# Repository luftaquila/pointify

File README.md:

# Pointify

DIY retro analog gauge meters that display system metrics in real time, including Claude usage stats!

<table>
  <tr>
    <td>
      
    </td>
    <td>
      <video src="https://github.com/user-attachments/assets/7dd133b8-86af-4e1a-b1fe-1c4ecdfecce1" controls></video>
    </td>
  </tr>
</table>

## Usage

Pointify Desktop runs on macOS, Windows, and Linux, driving up to 8 gauges with customizable metrics.

Its software gauges work without the device, but watching real needles twitch is way better. So go build one!

1. Install Pointify Desktop and open it.
    * **macOS / Linux (Homebrew)**
      ```bash
      brew tap luftaquila/pointify https://github.com/luftaquila/pointify
      brew install --cask pointify # macOS
      brew install pointify        # Linux
      ```
    * **Windows (Manual)**: Download from the [latest release](https://github.com/luftaquila/pointify/releases/latest).
1. Connect your Pointify to the computer and set up gauges to your preference.

<details>

<summary>Full list of supported metrics</summary>

- 🕹️ Hardware
  - CPU
    - Utilization
    - Temperature
    - Clock Frequency
    - Power Consumption
  - GPU
    - Utilization
    - Temperature
    - Clock Frequency
    - Power Consumption
    - VRAM Usage
  - Memory
    - RAM and Swap Usage
  - Network
    - RX, TX and RX/TX Speed
  - Disk
    - Usage
    - Read, Write and R/W Speed
- **🤖 Claude Usage Stats**
  - Usage Limits
    - 5h session limit and reset time
    - Weekly limit and reset time
  - Claude Code stats
    - Today's total tokens
    - Today's input, output and I/O tokens
    - Today's cache read and write tokens
    - Today's cost ($)

</details>

> [!NOTE]
> Some metrics have platform/hardware limitations.
> * **CPU Temperature and Power**: Not available on Windows.
> * **GPU metrics**: Not supported on AMD graphics cards.
> * **GPU VRAM Usage**: Not available on Apple Silicon.

### Optional setup

To fetch Claude usage limits (5h session and weekly), Pointify needs your browser credentials.

Claude Code stats are collected from local logs and do not require credentials.

> [!NOTE]
> Credentials are stored locally and only used to fetch usage data directly from Claude. No information is sent to any third-party server.
> See the `get_claude_usage` function in [lib.rs](https://github.com/luftaquila/pointify/blob/v2/gui/src-tauri/src/lib.rs) for details.

<details>

<summary>Firefox</summary>

1. Open Firefox and visit `https://claude.ai`. Log in if you haven't already.
1. Open Developer Tools (F12).
1. Go to the `Storage` tab.
1. On the left sidebar, click `Cookies` - `https://claude.ai`.
1. Locate the `cf_clearance`, `lastActiveOrg`, and `sessionKey` values.
1. Click the `Open .claude.env` button on the desktop app and paste the corresponding values.

</details>

<details>

<summary>Chrome</summary>

1. Open Chrome and visit `https://claude.ai`. Log in if you haven't already.
1. Open Developer Tools (F12).
1. Go to the `Application` tab.
1. On the left sidebar, click `Storage` - `Cookies` - `https://claude.ai`.
1. Locate the `cf_clearance`, `lastActiveOrg`, and `sessionKey` values.
1. Click the `Open .claude.env` button on the desktop app and paste the corresponding values.

</details>

## Do It Yourself!

Pointify is fully open-source and open-hardware. Build your own device at home!

### 1. Build PCB

1. Download `pointify-hardware.zip` from the [latest release](https://github.com/luftaquila/pointify/releases/latest) and unzip.
1. Gerber, BOM, and CPL files are in the `pcb/` directory. Use them to place a PCB assembly order from manufacturers such as JLCPCB.

### 2. Upload Firmware

If your board is fresh and the MCU has never been flashed, it will always boot into USB bootloader mode.

1. Connect your board to the computer.
1. Open Pointify Desktop and click the chip icon at the bottom of the sidebar.

`CURRENT` version will show as `Bootloader`. Click the `Update Firmware` button to flash it.

> [!NOTE]
> If your computer is running Windows and `CURRENT` shows as `N/A`, it means the CH372 driver is missing.
> Press the `Shift` key and the button will change to `Update Firmware (force)`.
> The force install process will automatically detect and install the missing driver.
> Alternatively, you can install the driver manually from [here](https://www.wch-ic.com/downloads/CH372DRV_EXE.html).

### 3. 3D-Print Housing and Assembly

#### Prerequisites

* 6x M2*8mm bolts
* 91C4 3V DC analog voltmeters, as many as you need
* Some wires and soldering skills
* 4x anti-slip pads with radius < 10mm

1. Download `pointify-hardware.zip` from the [latest release](https://github.com/luftaquila/pointify/releases/latest) and unzip.
1. 3D-print the STL files you need from the `3d/` directory.
1. Install the gauges into the housing.
1. Connect all negative terminals (near the 0V scale) of the gauge to the GND header on the PCB.
    * Daisy-chain them, since there's only one GND pad (marked ⏚).
1. Connect each positive terminal (near the 3V scale) to PWM port #1~8 on the PCB.
    * The pad right next to the GND is PWM1.
    * Solder directly to the washer that comes with the gauge, or crimp a ring terminal onto the wire. Crimping is easier to work with but you'll need a crimp tool and ring terminals.
1. Mount the PCB upside down onto the housing. The USB port faces downward.
1. Attach the back cover.

### 4. Customize Gauge Panel

Use the [Gauge Panel Generator](https://luftaquila.github.io/pointify/generator.html) to design and print your own gauge panel graphics.

Examples from the [device/gauge/example/](device/gauge/example) directory:

## Development

<details>

<summary>Open</summary>

### Desktop App

Requires [Node.js](https://nodejs.org/en/download) and [Rust](https://rust-lang.org/tools/install/).

```bash
cd gui
npm install
npm run tauri dev       # development
npm run tauri build     # production
```

### Firmware

Requires [nightly Rust](https://rust-lang.github.io/rustup/concepts/channels.html#working-with-nightly-rust).

```bash
cargo install wchisp --git https://github.com/ch32-rs/wchisp

cd device/firmware
cargo build --release   # build only
cargo run --release     # build + flash
```

</details>

<hr>
<br>

<picture>
  <source media="(prefers-color-scheme: dark)" srcset="https://api.star-history.com/svg?repos=luftaquila/pointify&type=Date&theme=dark" />
  <source media="(prefers-color-scheme: light)" srcset="https://api.star-history.com/svg?repos=luftaquila/pointify&type=Date" />
  
</picture>

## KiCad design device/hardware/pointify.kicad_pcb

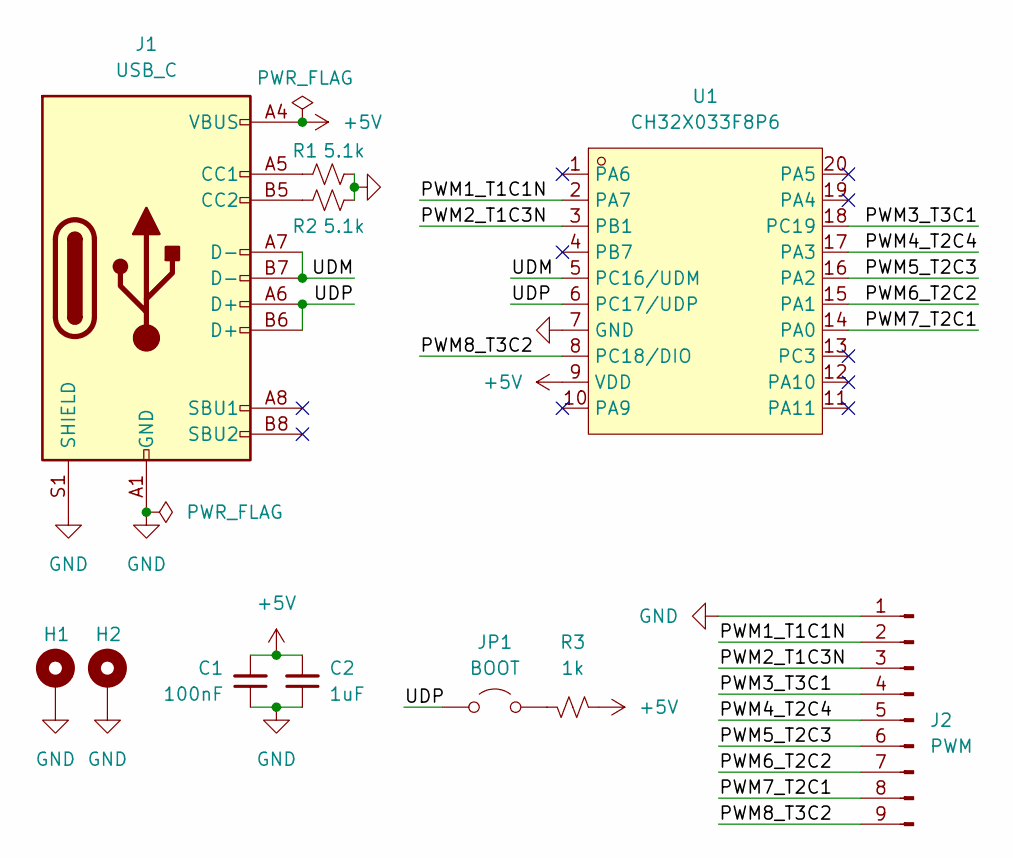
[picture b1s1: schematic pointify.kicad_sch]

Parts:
C1: 100nF; C_0402_1005Metric; LCSC C1525
C2: 1uF; C_0402_1005Metric; LCSC C52923
H1, H2: MountingHole_Pad; MountingHole_3.7mm_Pad_TopBottom; LCSC C2916384
J1: USB_C; USB_C_Receptacle_GCT_USB4105-xx-A_16P_TopMnt_Horizontal; LCSC C2927038
J2: PWM; PinHeader_1x09_P2.54mm_Vertical
JP1: BOOT; PinHeader_1x02_P2.00mm_Vertical
R1, R2: 5.1k; R_0402_1005Metric; LCSC C25905
R3: 1k; R_0402_1005Metric; LCSC C11702
U1: CH32X033F8P6; TSSOP-20_4.4x6.5mm_P0.65mm; LCSC Part C19268290

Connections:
+5V: C1.2, C2.2, J1.A4 (VBUS), J1.A9 (VBUS), J1.B4 (VBUS), J1.B9 (VBUS), R3.1, U1.9 (VDD)
/PWM1_T1C1N: J2.2, U1.2 (PA7)
/PWM2_T1C3N: J2.3, U1.3 (PB1)
/PWM3_T3C1: J2.4, U1.18 (PC19)
/PWM4_T2C4: J2.5, U1.17 (PA3)
/PWM5_T2C3: J2.6, U1.16 (PA2)
/PWM6_T2C2: J2.7, U1.15 (PA1)
/PWM7_T2C1: J2.8, U1.14 (PA0)
/PWM8_T3C2: J2.9, U1.8 (PC18/DIO)
/UDM: J1.A7 (D-), J1.B7 (D-), U1.5 (PC16/UDM)
/UDP: J1.A6 (D+), J1.B6 (D+), JP1.2 (B), U1.6 (PC17/UDP)
GND: C1.1, C2.1, H1.1, H2.1, J1.A1 (GND), J1.A12 (GND), J1.B1 (GND), J1.B12 (GND), J1.S1 (SHIELD), J2.1, R1.2, R2.2, U1.7 (GND)
unnamed: J1.A5 (CC1), R1.1
unnamed: J1.B5 (CC2), R2.1
unnamed: JP1.1 (A), R3.2

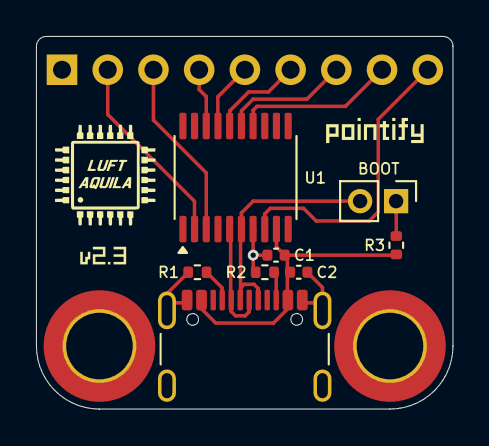
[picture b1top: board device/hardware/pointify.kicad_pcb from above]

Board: 2 copper layers, 23.1 x 20.7 mm, 11 parts (0 on the bottom side), 15 nets.

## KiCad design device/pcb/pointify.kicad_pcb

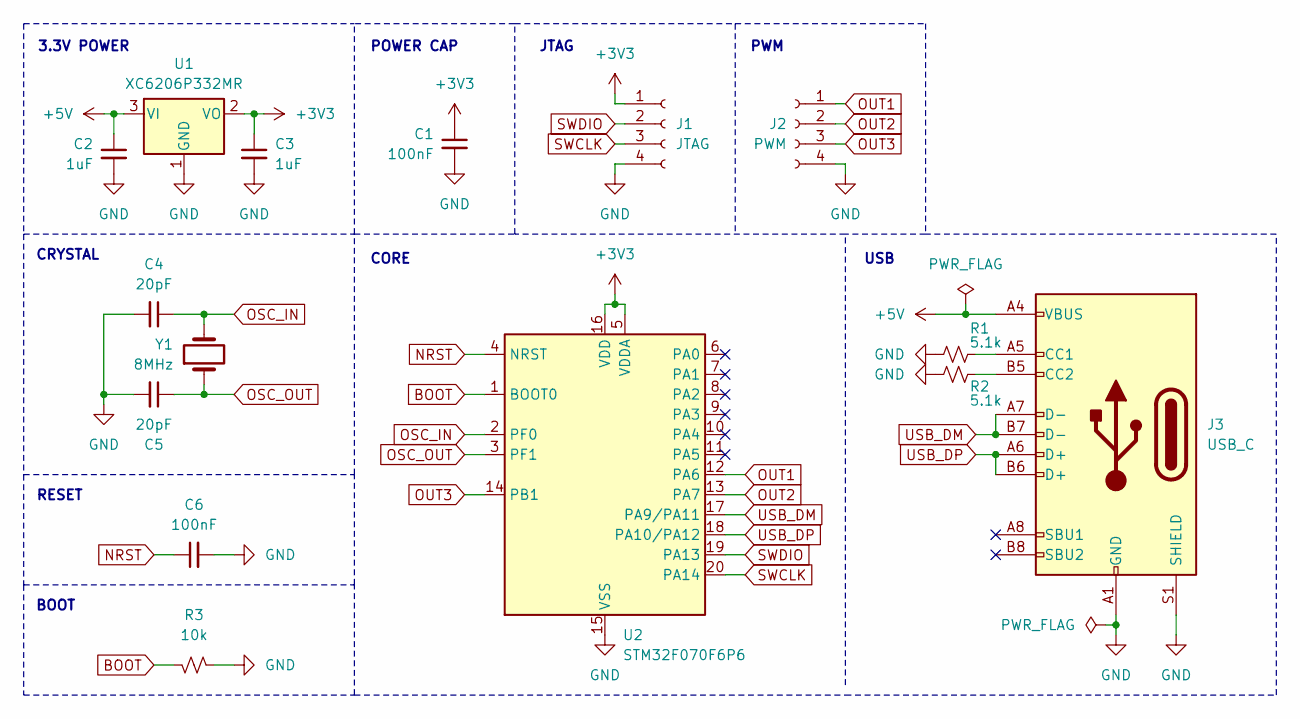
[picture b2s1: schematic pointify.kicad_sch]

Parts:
C1, C6: 100nF; C_0603_1608Metric; LCSC C14663
C2, C3: 1uF; C_0603_1608Metric; LCSC C15849
C4, C5: 20pF; C_0603_1608Metric; LCSC C1648
J1: JTAG; PinHeader_1x04_P1.27mm_Vertical
J2: PWM; PinHeader_1x04_P2.54mm_Vertical
J3: USB_C; USB_C_Receptacle_GCT_USB4105-xx-A_16P_TopMnt_Horizontal; LCSC C165948
R1, R2: 5.1k; R_0603_1608Metric; LCSC C23186
R3: 10k; R_0603_1608Metric; LCSC C25804
U1: XC6206P332MR; SOT-23-3; LCSC C5446
U2: STM32F070F6P6; TSSOP-20_4.4x6.5mm_P0.65mm; LCSC C86951
Y1: 8MHz; Crystal_SMD_5032-2Pin_5.0x3.2mm; LCSC C115962

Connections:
+3V3: C1.1, C3.1, J1.1, U1.2 (VO), U2.5 (VDDA), U2.16 (VDD)
+5V: C2.1, J3.A4 (VBUS), J3.A9 (VBUS), J3.B4 (VBUS), J3.B9 (VBUS), U1.3 (VI)
BOOT: R3.2, U2.1 (BOOT0)
GND: C1.2, C2.2, C3.2, C4.2, C5.2, C6.2, J1.4, J2.4, J3.A1 (GND), J3.A12 (GND), J3.B1 (GND), J3.B12 (GND), J3.S1 (SHIELD), R1.1, R2.1, R3.1, U1.1 (GND), U2.15 (VSS)
NRST: C6.1, U2.4 (NRST)
unnamed: J3.A5 (CC1), R1.2
unnamed: J3.B5 (CC2), R2.2
OSC_IN: C4.1, U2.2 (PF0), Y1.2
OSC_OUT: C5.1, U2.3 (PF1), Y1.1
OUT1: J2.1, U2.12 (PA6)
OUT2: J2.2, U2.13 (PA7)
OUT3: J2.3, U2.14 (PB1)
SWCLK: J1.3, U2.20 (PA14)
SWDIO: J1.2, U2.19 (PA13)
USB_DM: J3.A7 (D-), J3.B7 (D-), U2.17 (PA9/PA11)
USB_DP: J3.A6 (D+), J3.B6 (D+), U2.18 (PA10/PA12)

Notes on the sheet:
CRYSTAL
USB
POWER CAP
PWM
JTAG
3.3V POWER
CORE
BOOT
RESET

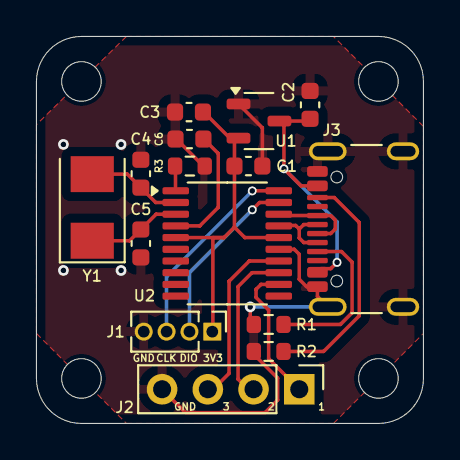
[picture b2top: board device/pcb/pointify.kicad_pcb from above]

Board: 2 copper layers, 21.5 x 21.5 mm, 15 parts (0 on the bottom side), 16 nets.

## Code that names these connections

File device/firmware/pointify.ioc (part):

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Mcu.Name=STM32F070F6Px
Mcu.Package=TSSOP20
Mcu.UserName=STM32F070F6Px
PA11.Mode=Device
PA11.Signal=USB_DM
PA12.Mode=Device
PA12.Signal=USB_DP
PA13.Mode=Serial_Wire
PA13.Signal=SYS_SWDIO
PA14.Mode=Serial_Wire
PA14.Signal=SYS_SWCLK
PA6.Signal=S_TIM3_CH1
PA7.Signal=S_TIM3_CH2
PB1.Signal=S_TIM3_CH4
PF0-OSC_IN.Mode=HSE-External-Oscillator
PF0-OSC_IN.Signal=RCC_OSC_IN
PF1-OSC_OUT.Mode=HSE-External-Oscillator
PF1-OSC_OUT.Signal=RCC_OSC_OUT
RCC.SYSCLKFreq_VALUE=48000000
RCC.SYSCLKSource=RCC_SYSCLKSOURCE_PLLCLK
board=custom

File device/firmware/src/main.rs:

#![no_std]
#![no_main]
#![feature(type_alias_impl_trait)]
#![feature(impl_trait_in_assoc_type)]

mod usb_cdc;

use ch32_hal as hal;
use embassy_executor::Spawner;
use hal::adc::{Adc, SampleTime, VrefInt};
use hal::time::Hertz;
use hal::timer::complementary_pwm::{ComplementaryPwm, ComplementaryPwmPin};
use hal::timer::low_level::CountingMode;
use hal::timer::simple_pwm::{PwmPin, SimplePwm};
use hal::timer::Channel;

#[embassy_executor::main(entry = "qingke_rt::entry")]
async fn main(_spawner: Spawner) -> ! {
    let mut config = hal::Config::default();
    config.rcc = hal::rcc::Config::SYSCLK_FREQ_48MHZ_HSI;
    let p = hal::init(config);

    // ADC
    let mut adc = Adc::new(p.ADC1, Default::default());
    let mut vrefint = VrefInt;
    let vref_raw = adc.convert(&mut vrefint, SampleTime::CYCLES11) as u32;
    let is_5v_supply = vref_raw < 1200;

    // TIM2 remap=0: PA0, PA1, PA2, PA3
    let ch1 = PwmPin::new_ch1::<0>(p.PA0);
    let ch2 = PwmPin::new_ch2::<0>(p.PA1);
    let ch3 = PwmPin::new_ch3::<0>(p.PA2);
    let ch4 = PwmPin::new_ch4::<0>(p.PA3);
    let mut pwm_tim2 = SimplePwm::new(
        p.TIM2, Some(ch1), Some(ch2), Some(ch3), Some(ch4),
        Hertz::khz(1), CountingMode::default(),
    );
    pwm_tim2.enable(Channel::Ch1);
    pwm_tim2.enable(Channel::Ch2);
    pwm_tim2.enable(Channel::Ch3);
    pwm_tim2.enable(Channel::Ch4);

    // Release PC18/DIO and PC19/DCK debug pins for GPIO/timer use
    // AFIO_PCFR1 bits[26:24] = sw_cfg = 0b100 (disable debug, release both pins)
    unsafe {
        let afio_pcfr1 = 0x4001_0004 as *mut u32;
        let val = afio_pcfr1.read_volatile();
        afio_pcfr1.write_volatile((val & !(0x07 << 24)) | (0x04 << 24));
    }

    // TIM3 remap=2: PC19(CH1), PC18(CH2)
    let ch1_t3 = PwmPin::new_ch1::<2>(p.PC19);
    let ch2_t3 = PwmPin::new_ch2::<2>(p.PC18);
    let mut pwm_tim3 = SimplePwm::new(
        p.TIM3, Some(ch1_t3), Some(ch2_t3), None, None,
        Hertz::khz(1), CountingMode::default(),
    );
    pwm_tim3.enable(Channel::Ch1);
    pwm_tim3.enable(Channel::Ch2);

    // TIM1 remap=1: PA7(CH1N), PB1(CH3N)
    let ch1n = ComplementaryPwmPin::new_ch1::<1>(p.PA7);
    let ch3n = ComplementaryPwmPin::new_ch3::<1>(p.PB1);
    let mut pwm_tim1 = ComplementaryPwm::new(
        p.TIM1, None, Some(ch1n), None, None, None, Some(ch3n), None,
        Hertz::khz(1), CountingMode::default(),
    );
    pwm_tim1.set_dead_time(0);
    pwm_tim1.enable(Channel::Ch1);
    pwm_tim1.enable(Channel::Ch3);

    // HAL ComplementaryPwm doesn't work properly with N-only channels.
    // Configure TIM1 entirely via raw registers.
    const TIM1: usize = 0x4001_2C00;
    unsafe {
        // CR1: CEN (bit 0) = 1 — start counter
        let cr1 = (TIM1 + 0x00) as *mut u32;
        let v = cr1.read_volatile();
        cr1.write_volatile(v | 1);
        // CCMR1: OC1M = PWM mode 2 (0b111), OC1PE = 1
        let ccmr1 = (TIM1 + 0x18) as *mut u32;
        let v = ccmr1.read_volatile();
        ccmr1.write_volatile((v & !(0x7 << 4)) | (0x7 << 4) | (1 << 3));
        // CCMR2: OC3M = PWM mode 2 (0b111), OC3PE = 1
        let ccmr2 = (TIM1 + 0x1C) as *mut u32;
        let v = ccmr2.read_volatile();
        ccmr2.write_volatile((v & !(0x7 << 4)) | (0x7 << 4) | (1 << 3));
        // CCER: CC1NE (bit 2) = 1, CC3NE (bit 10) = 1
        let ccer = (TIM1 + 0x20) as *mut u32;
        let v = ccer.read_volatile();
        ccer.write_volatile(v | (1 << 2) | (1 << 10));
        // BDTR: MOE (bit 15) = 1
        let bdtr = (TIM1 + 0x44) as *mut u32;
        let v = bdtr.read_volatile();
        bdtr.write_volatile(v | (1 << 15));
    }

    usb_cdc::usb_init();

    let max_duty_tim2 = pwm_tim2.get_max_duty();
    let max_duty_tim3 = pwm_tim3.get_max_duty();
    let max_duty_tim1 = unsafe { ((TIM1 + 0x2C) as *const u32).read_volatile() as u16 }; // ARR

    let mut rx_buf = [0u8; 64];
    loop {
        if let Some(len) = usb_cdc::usb_poll(&mut rx_buf) {
            for chunk in rx_buf[..len].chunks_exact(2) {
                let raw = u16::from_be_bytes([chunk[0], chunk[1]]);
                let is_5v_gauge = (raw & 0x8000) != 0;
                let index = ((raw >> 10) & 0x1F) as u8;
                let value = raw & 0x3FF;
                let scale_3v = is_5v_supply && !is_5v_gauge;

                match index {
                    0 => unsafe { ((TIM1 + 0x34) as *mut u32).write_volatile(duty_u16(value, max_duty_tim1, scale_3v) as u32) }, // CCR1 (PA7)
                    1 => unsafe { ((TIM1 + 0x3C) as *mut u32).write_volatile(duty_u16(value, max_duty_tim1, scale_3v) as u32) }, // CCR3 (PB1)
                    2 => pwm_tim3.set_duty(Channel::Ch1, duty_u32(value, max_duty_tim3, scale_3v)),
                    7 => pwm_tim3.set_duty(Channel::Ch2, duty_u32(value, max_duty_tim3, scale_3v)),
                    3 => pwm_tim2.set_duty(Channel::Ch4, duty_u32(value, max_duty_tim2, scale_3v)),
                    4 => pwm_tim2.set_duty(Channel::Ch3, duty_u32(value, max_duty_tim2, scale_3v)),
                    5 => pwm_tim2.set_duty(Channel::Ch2, duty_u32(value, max_duty_tim2, scale_3v)),
                    6 => pwm_tim2.set_duty(Channel::Ch1, duty_u32(value, max_duty_tim2, scale_3v)),
                    31 if value == 0x3FF => {
                        // Zero all PWMs as visual confirmation before bootloader
                        pwm_tim2.set_duty(Channel::Ch1, 0);
                        pwm_tim2.set_duty(Channel::Ch2, 0);
                        pwm_tim2.set_duty(Channel::Ch3, 0);
                        pwm_tim2.set_duty(Channel::Ch4, 0);
                        pwm_tim3.set_duty(Channel::Ch1, 0);
                        pwm_tim3.set_duty(Channel::Ch2, 0);
                        unsafe { ((TIM1 + 0x34) as *mut u32).write_volatile(0) }; // CCR1
                        unsafe { ((TIM1 + 0x3C) as *mut u32).write_volatile(0) }; // CCR3
                        usb_cdc::enter_bootloader();
                    }
                    _ => {}
                }
            }
        }
    }
}

fn duty_u32(value: u16, max_duty: u32, scale_3v: bool) -> u32 {
    if scale_3v {
        (value as u32 * max_duty * 3) / (1023 * 5)
    } else {
        (value as u32 * max_duty) / 1023
    }
}

fn duty_u16(value: u16, max_duty: u16, scale_3v: bool) -> u16 {
    if scale_3v {
        ((value as u32 * max_duty as u32 * 3) / (1023 * 5)) as u16
    } else {
        ((value as u32 * max_duty as u32) / 1023) as u16
    }
}

#[panic_handler]
fn panic(_info: &core::panic::PanicInfo) -> ! {
    loop {}
}

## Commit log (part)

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2024-11-23 add: tauri template
2024-11-23 add: default firmware setup
2024-11-23 fix: linker script and min stack size
2024-11-23 add: schematic prototype
2024-11-23 add: 3d models from https://github.com/luftaquila/hardware-meter
2024-11-23 add: github funding
2024-11-23 update: utility base path
2024-11-24 add: complete pcb artwork
2024-11-29 add: openocd program command
2024-11-29 update: CubeMX version and USBD descriptor
2024-11-29 update: set timer period for PWM
2026-02-06 add: gui app template
2026-02-06 impl: gauges
2026-02-06 impl: improved ui and config
2026-02-06 impl: fetch claude usage
2026-02-06 improve: add claude refresh rate and serial selector
2026-02-06 add: claude reset gauge
2026-02-06 improve: misc ui configs
2026-02-06 improve: use dev name on target
2026-02-06 bump: cargo crates
2026-02-06 impl: Apple Silicon GPU support
2026-02-09 fix: open text on macos
2026-02-09 update: cargo fmt
2026-02-09 impl: serial port
2026-02-13 add: v2 pcb
2026-02-13 add: template firmware
2026-02-13 impl: firmware
2026-02-13 update: max gauge count to 10, refrech claude only if gauge exists
2026-02-13 pcb v2.1: fix pinmaps
2026-02-13 update: translate font to polygons
2026-02-14 add: CPU Power metric
2026-02-14 add: release workflows
2026-02-15 update: app icon
2026-02-16 add: openscad 3d housing
2026-02-16 add: 3d model generation workflow
2026-02-17 fix: gauge m3 bolt clearance hole diameter
2026-02-17 update: format scad
2026-02-17 impl: claude code metrics
2026-02-18 update: max gauge count to 7
2026-02-18 add: images
2026-02-18 update: README
2026-02-18 fix: adjust gauge angle and tolerance
2026-02-18 add: anti-slip sticker placeholder
2026-02-19 fix: screw tab distance
2026-02-19 fix: claude code usage stats
2026-02-26 impl: firmware update
2026-02-26 improve: device detection
2026-02-26 fix: TIM1 channels
2026-02-26 update: fine-tune 3d model
2026-02-26 update: pcb v2.2
2026-02-26 update: release artifacts
2026-03-04 update: skip CI on v2 when caches are warm and remove redundant caches
2026-03-05 add: default gauge background panel graphic
2026-03-05 impl: gauge graphic customizer
2026-03-05 add: example gallery
2026-03-05 add: 3d housing gallery
2026-03-11 add: overshoot toggle to allow gauge needle past full-scale mark
2026-03-11 add: Homebrew tap for macOS (Cask) and Linux (Formula) installation
2026-03-11 fix: prevent duplicate CI cache on tag releases
2026-03-19 brew: update to 2.4.0
2026-03-19 brew: update to 2.4.1
2026-03-22 chore: update docs
2026-03-22 update: pcb v2.3 with PWM8
2026-03-22 brew: update to 2.5.0
2026-03-25 fix: port-cover align
2026-04-20 brew: update to 2.5.1
2026-04-20 brew: update to 2.6.0
2026-04-23 feat: unify Claude metric selector with target sub-options
    Expose new Claude usage buckets (extra_usage, seven_day_omelette as
    "Claude Design", seven_day_sonnet) and collapse Limit/Reset and
    claude_code_* variants into single metrics whose Limit/Reset or
    token/cost target is chosen via the sub-option dropdown.
2026-04-23 brew: update to 2.7.0
2026-04-27 brew: update to 2.8.0
2026-04-27 feat: rename Account to User and swap order with Target
2026-05-11 brew: update to 2.8.1
